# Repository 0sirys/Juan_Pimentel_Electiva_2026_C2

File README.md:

# Juan_Pimentel_Electiva_2026_C2

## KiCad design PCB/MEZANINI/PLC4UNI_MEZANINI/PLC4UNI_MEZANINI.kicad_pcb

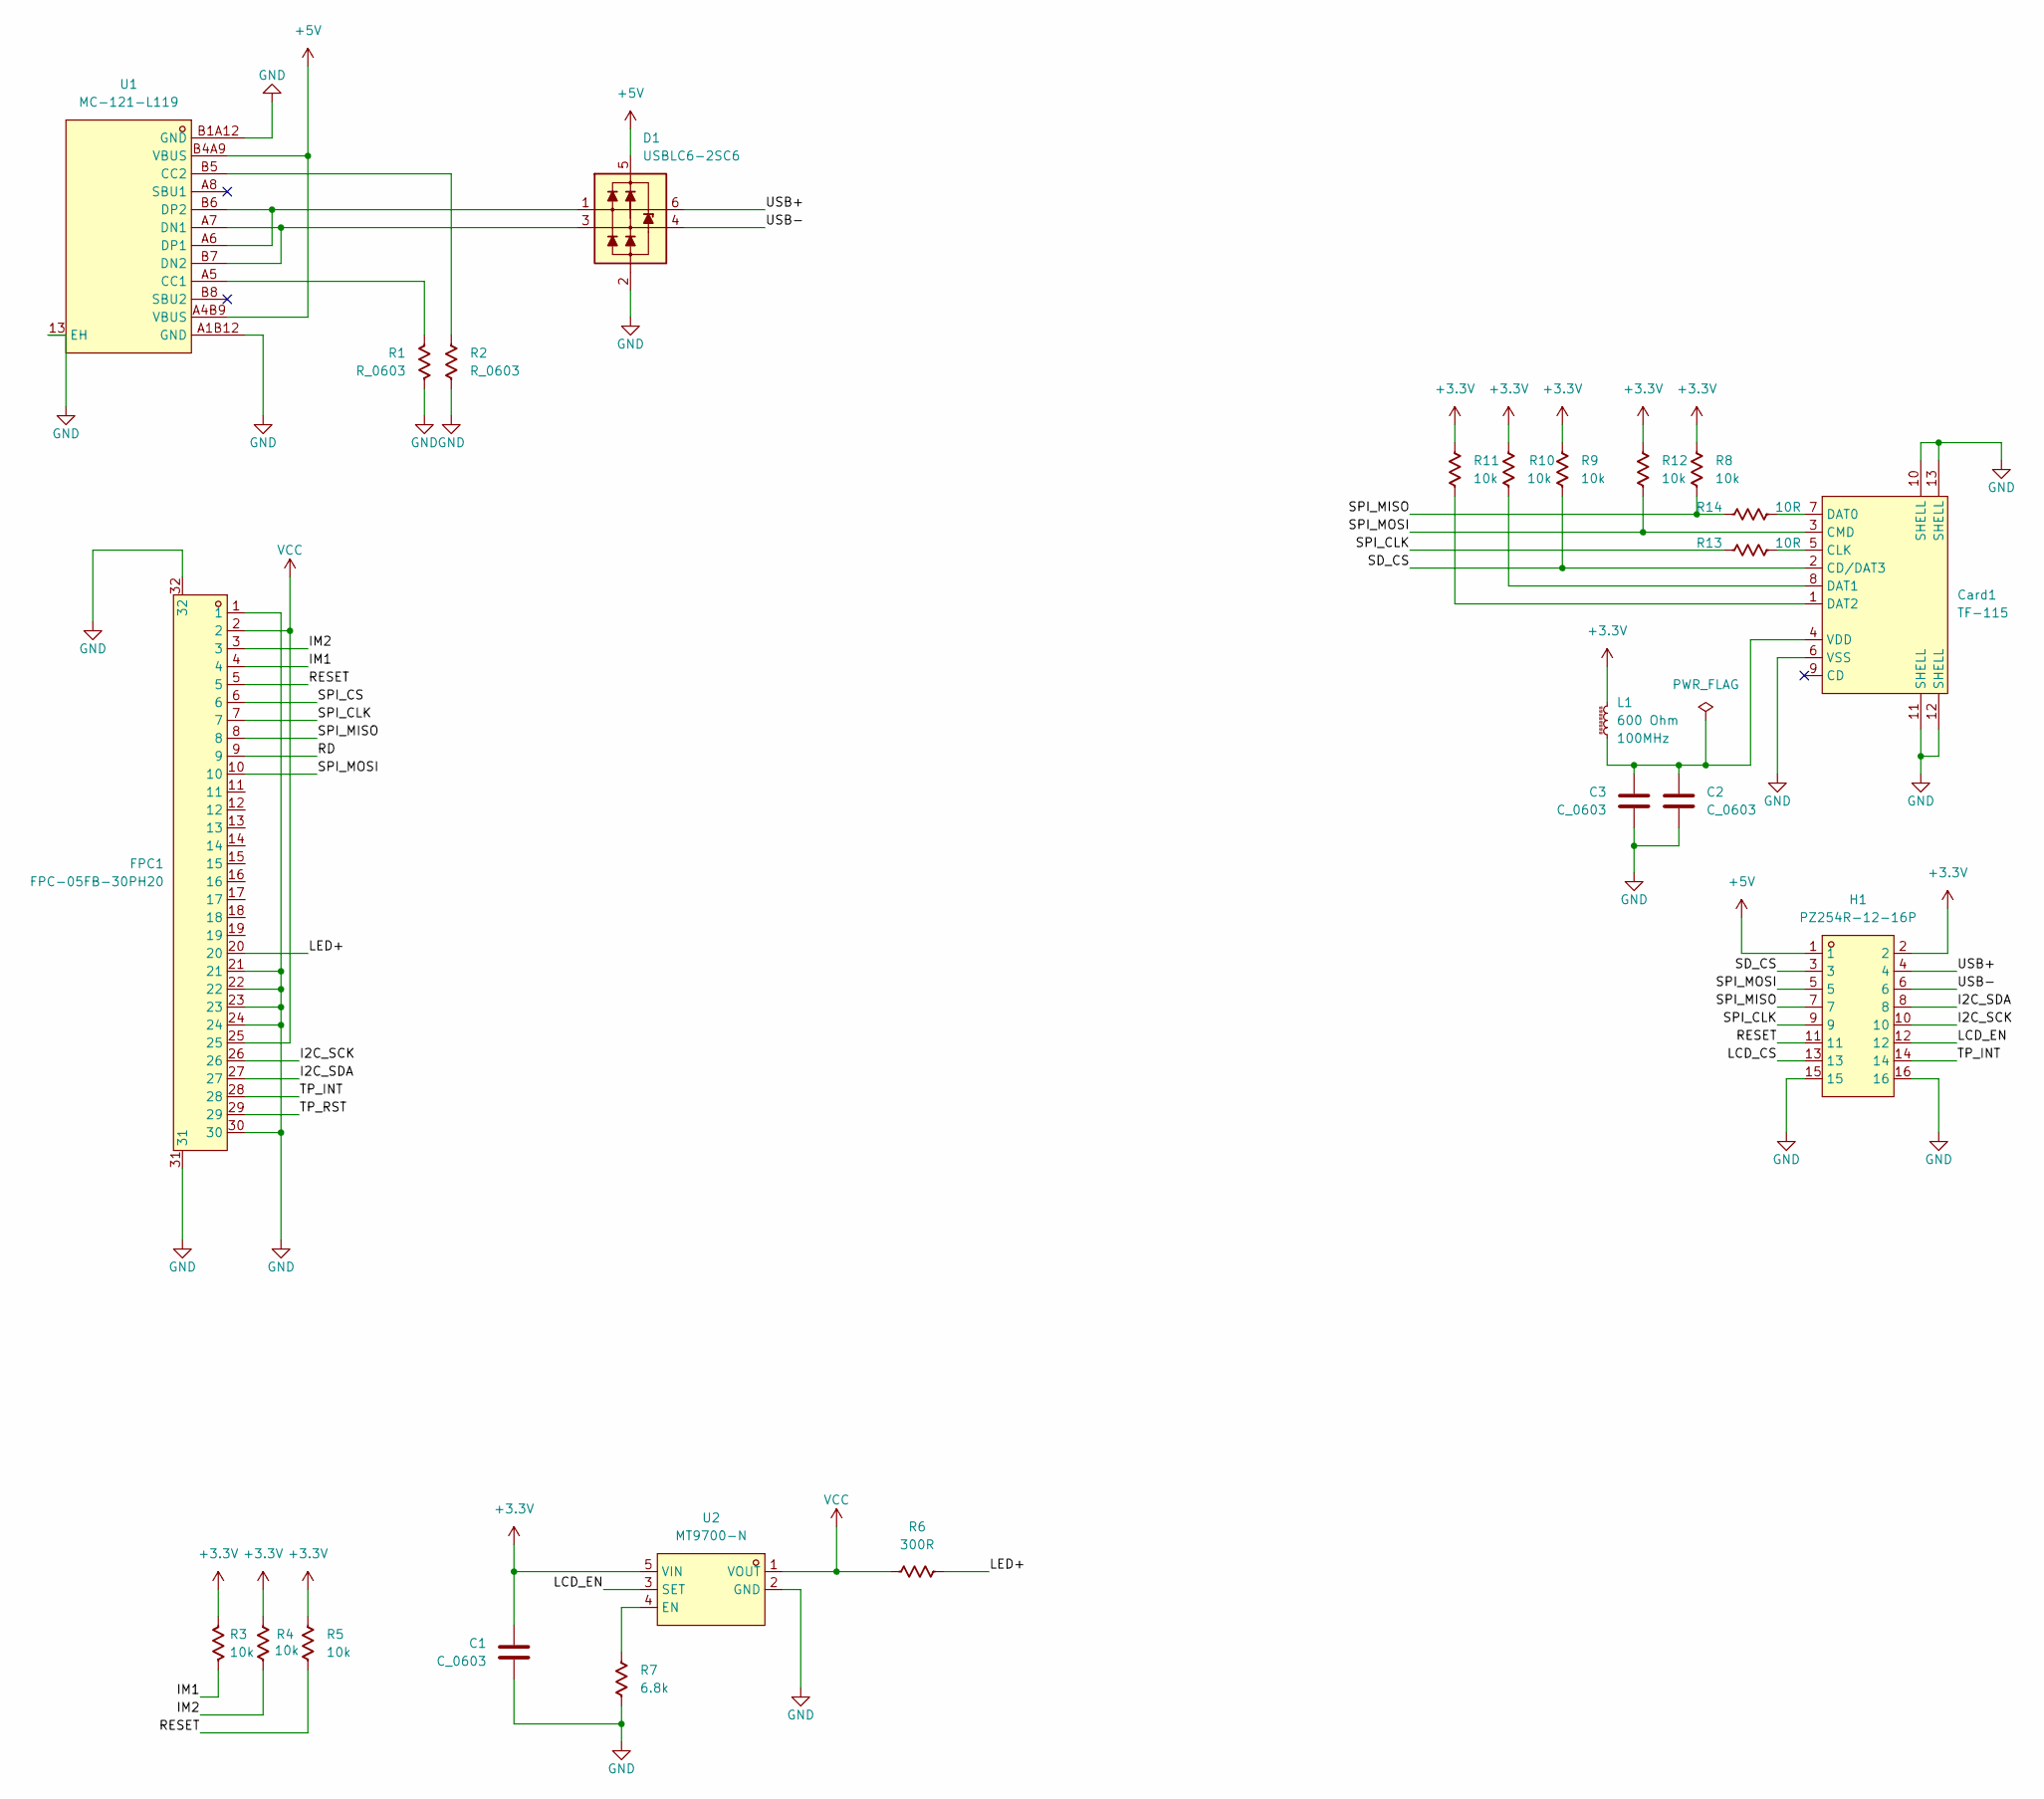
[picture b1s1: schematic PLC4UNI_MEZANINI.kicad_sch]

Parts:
C1, C2, C3: C_0603; C_0603_1608Metric
Card1: TF-115; TF-SMD_TF-115; MPN TF-115; LCSC Part C266620
D1: USBLC6-2SC6; SOT-23-6
FPC1: FPC-05FB-30PH20; FPC-SMD_30P-P0.50_FPC-05FB-30PH20; MPN FPC-05FB-30PH20; LCSC Part C2856833
H1: PZ254R-12-16P; HDR-TH_16P-P2.54-H-M-R2-C8-S2.54; MPN PZ254R-12-16P; LCSC Part C492436
L1: 600 Ohm; C_0805_2012Metric
R1, R2: R_0603; R_0603_1608Metric
R3, R4, R5, R8, R9, R10, R11, R12: 10k; R_0603_1608Metric
R6: 300R; R_0603_1608Metric
R7: 6.8k; R_0603_1608Metric
R13, R14: 10R; R_0603_1608Metric
U1: MC-121-L119; USB-C-SMD_HANBO_MC-121-L119; MPN MC-121-L119; LCSC Part C6332278
U2: MT9700-N; SOT-23-5_L2.9-W1.6-P0.95-LS2.9-BL; MPN MT9700-N; LCSC Part C42441843

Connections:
+3.3V: C1.1, H1.2, L1.2, R3.1, R4.1, R5.1, R8.1, R9.1, R10.1, R11.1, R12.1, U2.5 (VIN)
+5V: D1.5 (VP), H1.1, U1.A4B9 (VBUS), U1.B4A9 (VBUS)
/I2C_SCK: FPC1.26, H1.10
/I2C_SDA: FPC1.27, H1.8
/IM1: FPC1.4, R3.2
/IM2: FPC1.3, R4.2
/LCD_CS: H1.13
/LCD_EN: H1.12, U2.3 (SET)
/LED+: FPC1.20, R6.2
/RD: FPC1.9
/RESET: FPC1.5, H1.11, R5.2
/SD_CS: Card1.2 (CD/DAT3), H1.3, R9.2
/SPI_CLK: FPC1.7, H1.9, R13.1
/SPI_CS: FPC1.6
/SPI_MISO: FPC1.8, H1.7, R8.2, R14.1
/SPI_MOSI: Card1.3 (CMD), FPC1.10, H1.5, R12.2
/TP_INT: FPC1.28, H1.14
/TP_RST: FPC1.29
/USB+: D1.6 (L1), H1.4
/USB-: D1.4 (L2), H1.6
GND: C1.2, C2.2, C3.2, Card1.6 (VSS), Card1.10 (SHELL), Card1.11 (SHELL), Card1.12 (SHELL), Card1.13 (SHELL), D1.2 (VN), FPC1.1, FPC1.21, FPC1.22, FPC1.23, FPC1.24, FPC1.30, FPC1.31, FPC1.32, H1.15, H1.16, R1.2, R2.2, R7.1, U1.13 (EH), U1.A1B12 (GND), U1.B1A12 (GND), U2.2 (GND)
unnamed: Card1.5 (CLK), R13.2
unnamed: Card1.7 (DAT0), R14.2
unnamed: Card1.8 (DAT1), R10.2
unnamed: Card1.1 (DAT2), R11.2
unnamed: C2.1, C3.1, Card1.4 (VDD), L1.1
unnamed: R1.1, U1.A5 (CC1)
unnamed: R2.1, U1.B5 (CC2)
unnamed: D1.3 (L2), U1.A7 (DN1), U1.B7 (DN2)
unnamed: D1.1 (L1), U1.A6 (DP1), U1.B6 (DP2)
unnamed: R7.2, U2.4 (EN)
VCC: FPC1.2, FPC1.25, R6.1, U2.1 (VOUT)

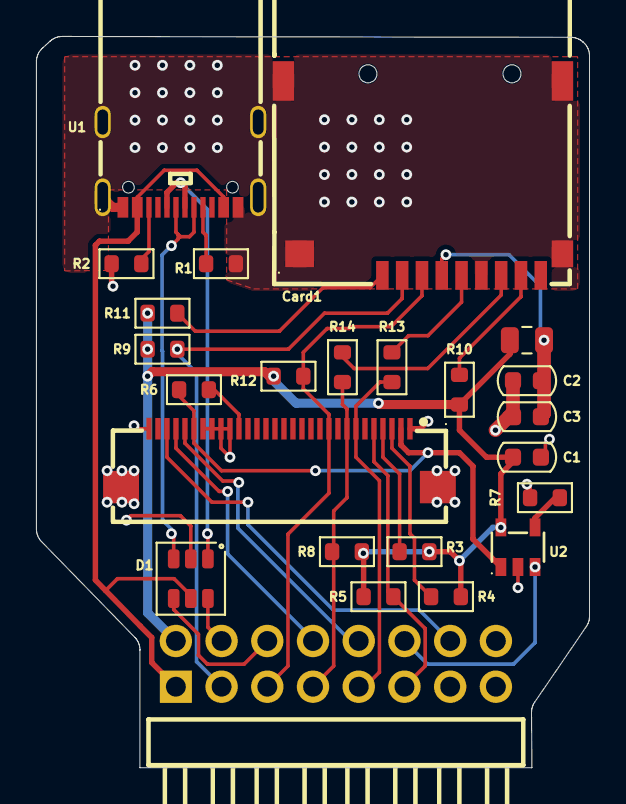
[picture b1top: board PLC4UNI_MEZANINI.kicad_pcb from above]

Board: 2 copper layers, 30.7 x 40.6 mm, 24 parts (0 on the bottom side), 28 nets.

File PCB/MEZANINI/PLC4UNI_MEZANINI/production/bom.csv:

Designator,Footprint,Quantity,Value,LCSC Part #
"C1, C2, C3",0603,3,C_0603,
CARD1,TF-SMD_TF-115,1,TF-115,C266620
D1,SOT-23-6,1,USBLC6-2SC6,
FPC1,FPC-SMD_30P-P0.50_FPC-05FB-30PH20,1,FPC-05FB-30PH20,C2856833
H1,HDR-TH_16P-P2.54-H-M-R2-C8-S2.54,1,PZ254R-12-16P,C492436
L1,0805,1,600 Ohm,
"R1, R2",0603,2,R_0603,
"R10, R11, R12, R3, R4, R5, R8, R9",0603,8,10k,
"R13, R14",0603,2,10R,
R6,0603,1,300R,
R7,0603,1,6.8k,
U1,USB-C-SMD_HANBO_MC-121-L119,1,MC-121-L119,C6332278
U2,SOT-23-5_L2.9-W1.6-P0.95-LS2.9-BL,1,MT9700-N,C42441843

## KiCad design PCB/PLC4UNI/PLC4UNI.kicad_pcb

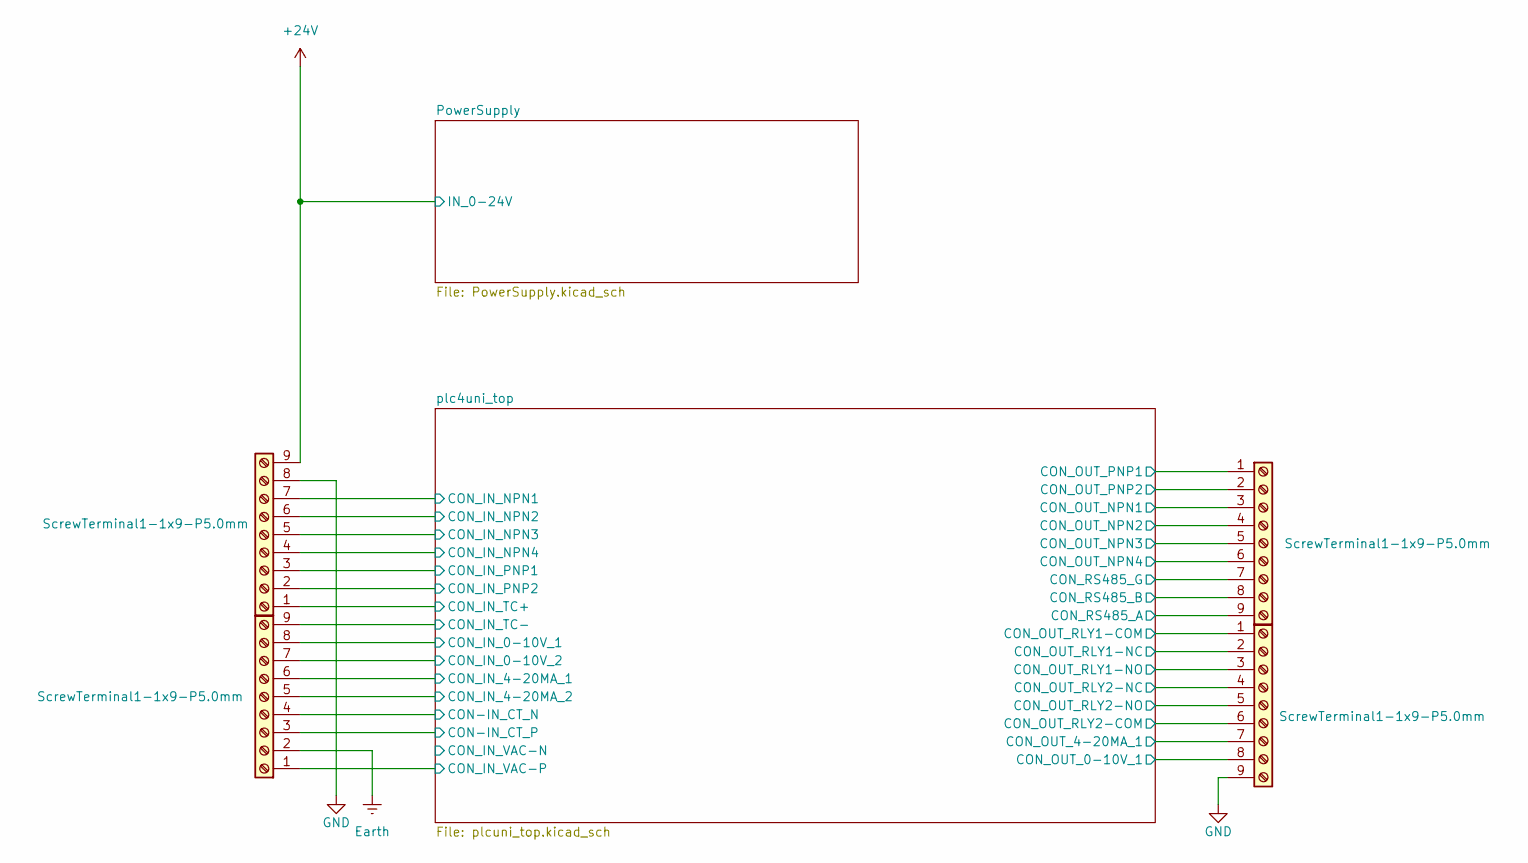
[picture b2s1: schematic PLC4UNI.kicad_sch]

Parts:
U1, U2, U3, U4: ScrewTerminal1-1x9-P5.0mm; CONN-TH_9P-P5.00_DB127V-5.0-9P-GN-S; MPN DB127V-5.0-9P-GN-S; LCSC Part C430627

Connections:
+24V: U1.9; also elsewhere on the board
/plc4uni_top/CON-IN_CT_N: U2.4; also elsewhere on the board
/plc4uni_top/CON-IN_CT_P: U2.3; also elsewhere on the board
/plc4uni_top/CON_IN_0-10V_1: U2.8; also elsewhere on the board
/plc4uni_top/CON_IN_0-10V_2: U2.7; also elsewhere on the board
/plc4uni_top/CON_IN_4-20MA_1: U2.6; also elsewhere on the board
/plc4uni_top/CON_IN_4-20MA_2: U2.5; also elsewhere on the board
/plc4uni_top/CON_IN_NPN1: U1.7; also elsewhere on the board
/plc4uni_top/CON_IN_NPN2: U1.6; also elsewhere on the board
/plc4uni_top/CON_IN_NPN3: U1.5; also elsewhere on the board
/plc4uni_top/CON_IN_NPN4: U1.4; also elsewhere on the board
/plc4uni_top/CON_IN_PNP1: U1.3; also elsewhere on the board
/plc4uni_top/CON_IN_PNP2: U1.2; also elsewhere on the board
/plc4uni_top/CON_IN_TC+: U1.1; also elsewhere on the board
/plc4uni_top/CON_IN_TC-: U2.9; also elsewhere on the board
/plc4uni_top/CON_IN_VAC-P: U2.1; also elsewhere on the board
/plc4uni_top/CON_OUT_0-10V_1: U4.8; also elsewhere on the board
/plc4uni_top/CON_OUT_4-20MA_1: U4.7; also elsewhere on the board
/plc4uni_top/CON_OUT_NPN1: U3.3; also elsewhere on the board
/plc4uni_top/CON_OUT_NPN2: U3.4; also elsewhere on the board
/plc4uni_top/CON_OUT_NPN3: U3.5; also elsewhere on the board
/plc4uni_top/CON_OUT_NPN4: U3.6; also elsewhere on the board
/plc4uni_top/CON_OUT_PNP1: U3.1; also elsewhere on the board
/plc4uni_top/CON_OUT_PNP2: U3.2; also elsewhere on the board
/plc4uni_top/CON_OUT_RLY1-COM: U4.1; also elsewhere on the board
/plc4uni_top/CON_OUT_RLY1-NC: U4.2; also elsewhere on the board
/plc4uni_top/CON_OUT_RLY1-NO: U4.3; also elsewhere on the board
/plc4uni_top/CON_OUT_RLY2-COM: U4.6; also elsewhere on the board
/plc4uni_top/CON_OUT_RLY2-NC: U4.4; also elsewhere on the board
/plc4uni_top/CON_OUT_RLY2-NO: U4.5; also elsewhere on the board
/plc4uni_top/CON_RS485_A: U3.9; also elsewhere on the board
/plc4uni_top/CON_RS485_B: U3.8; also elsewhere on the board
/plc4uni_top/CON_RS485_G: U3.7; also elsewhere on the board
Earth: U2.2; also elsewhere on the board
GND: U1.8, U4.9; also elsewhere on the board

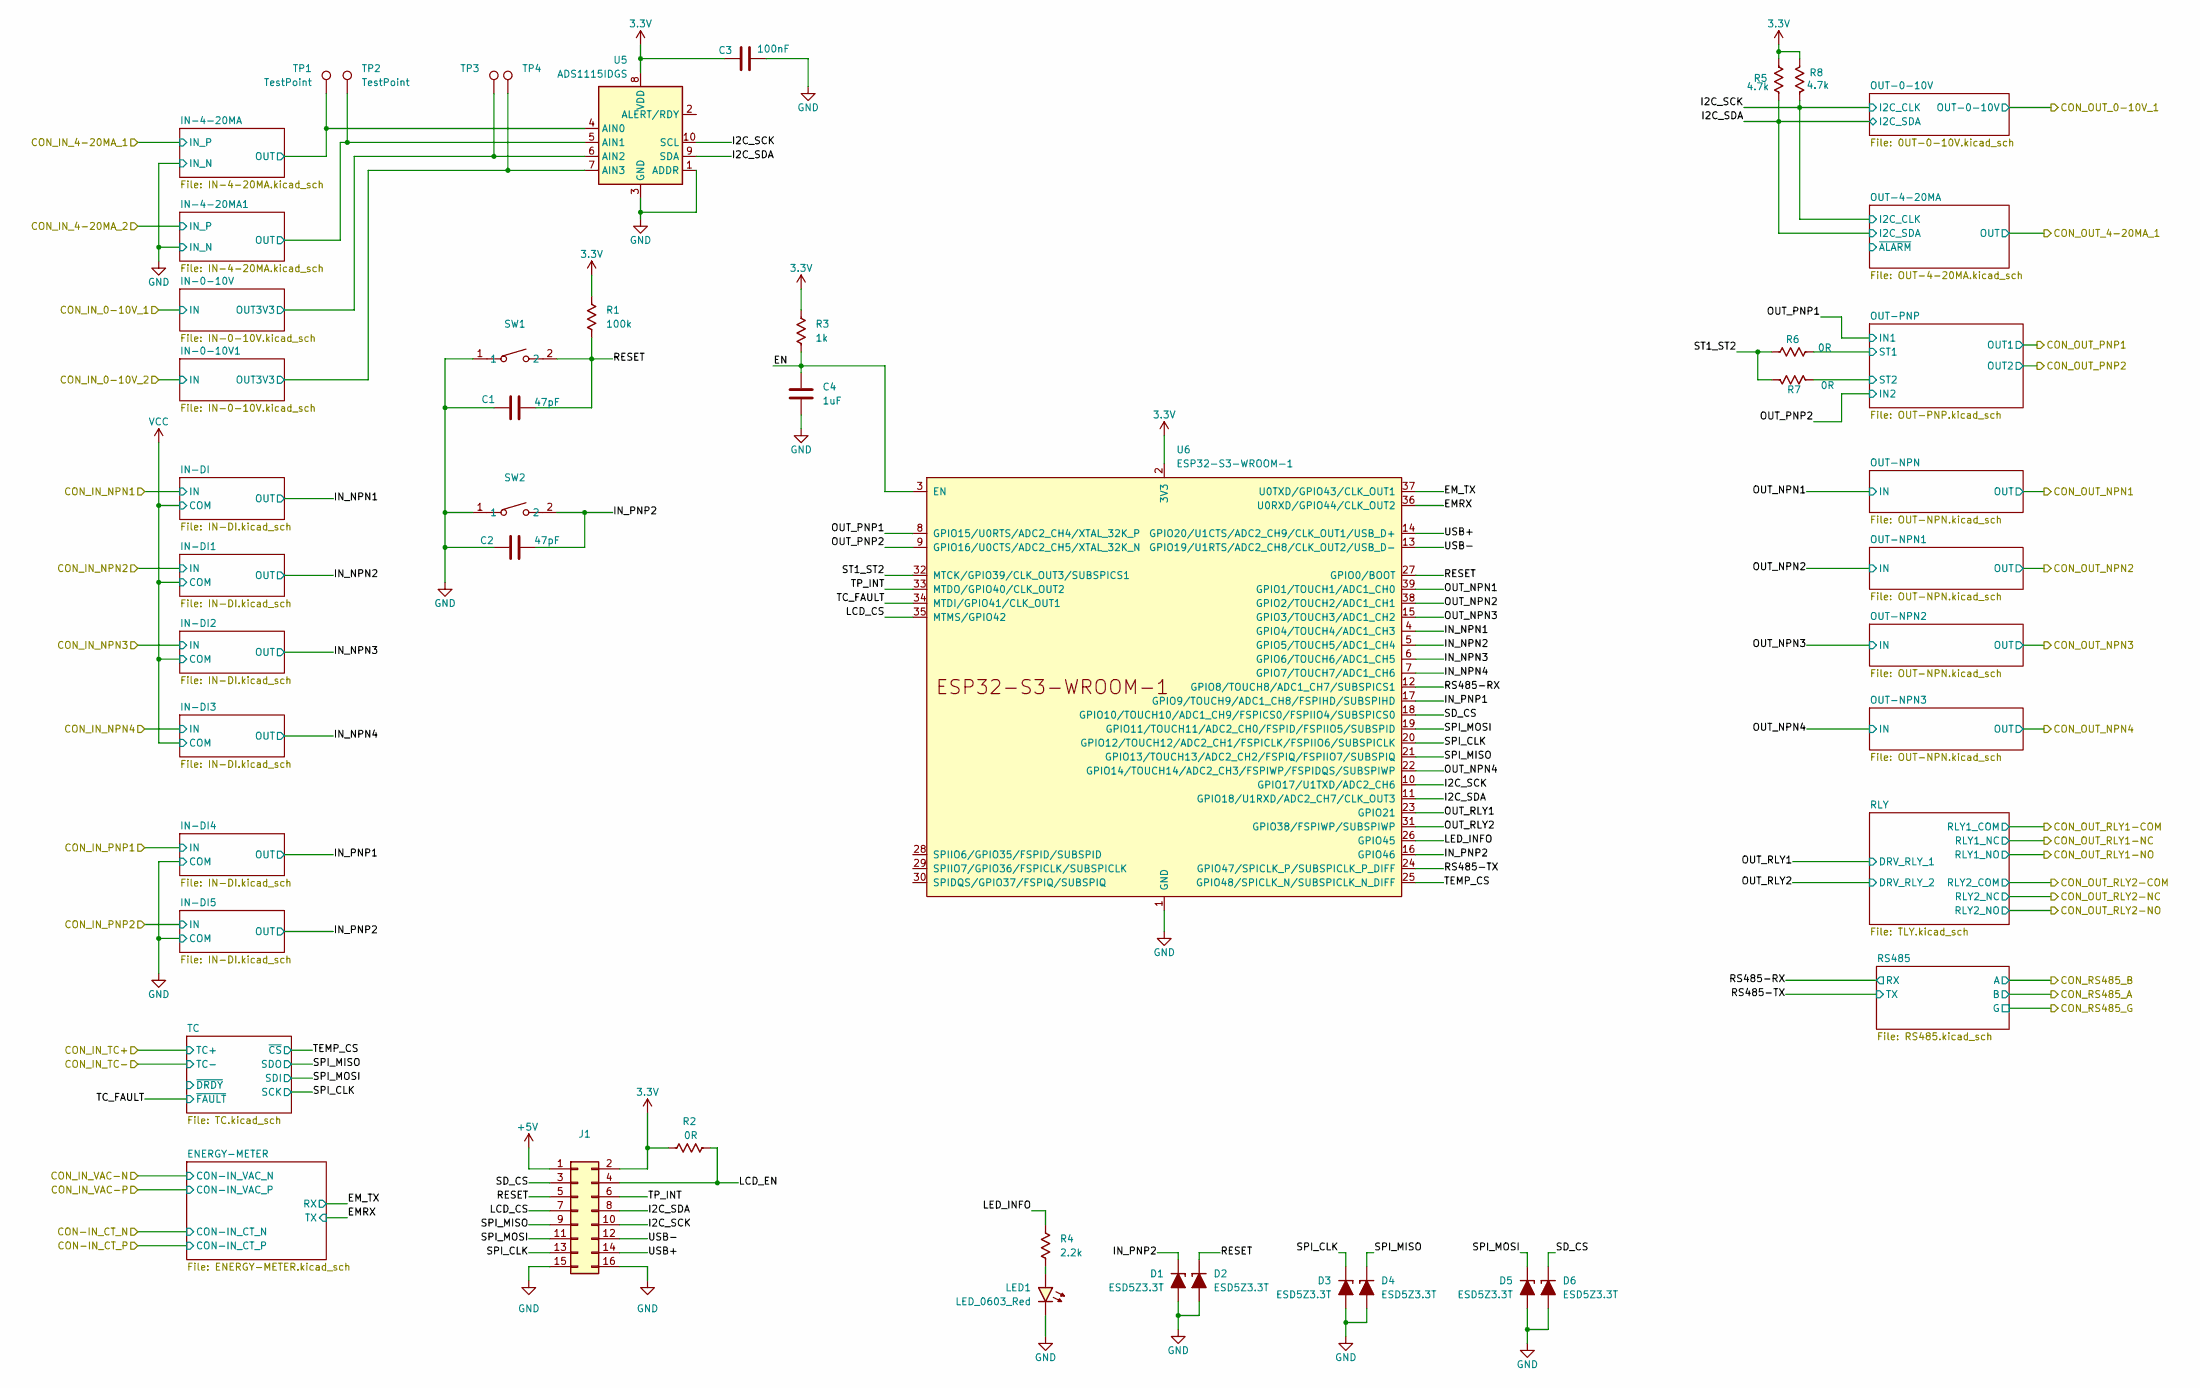
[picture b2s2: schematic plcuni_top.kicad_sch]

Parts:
C1, C2: 47pF; C_0603_1608Metric
C3: 100nF; C_0603_1608Metric
C4: 1uF; C_0603_1608Metric
D1, D2, D3, D4, D5, D6: ESD5Z3.3T; D_SOD-523
J1: Conn_02x08_Odd_Even; PinHeader_2x08_P2.54mm_Vertical
LED1: LED_0603_Red; LED_0603_1608Metric
R1: 100k; R_0603_1608Metric
R2, R6, R7: 0R; R_0603_1608Metric
R3: 1k; R_0603_1608Metric
R4: 2.2k; R_0603_1608Metric
R5, R8: 4.7k; R_0603_1608Metric
SW1, SW2: TS-1088-AR02016; SW-SMD_L3.9-W3.0-P4.45; MPN TS-1088-AR02016; LCSC Part C720477
TP1, TP2, TP3, TP4: TestPoint; TestPoint_THTPad_D1.5mm_Drill0.7mm
U5: ADS1115IDGS; TSSOP-10_3x3mm_P0.5mm
U6: ESP32-S3-WROOM-1

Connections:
3.3V: C3.1, J1.2, R1.1, R2.1, R3.1, R5.2, R8.2, U5.8 (VDD), U6.2 (3V3); also elsewhere on the board
/plc4uni_top/EMRX: U6.36 (U0RXD/GPIO44/CLK_OUT2); also elsewhere on the board
/plc4uni_top/EM_TX: U6.37 (U0TXD/GPIO43/CLK_OUT1); also elsewhere on the board
/plc4uni_top/EN: C4.1, R3.2, U6.3 (EN)
/plc4uni_top/I2C_SCK: J1.10, R8.1, U5.10 (SCL), U6.10 (GPIO17/U1TXD/ADC2_CH6); also elsewhere on the board
/plc4uni_top/I2C_SDA: J1.8, R5.1, U5.9 (SDA), U6.11 (GPIO18/U1RXD/ADC2_CH7/CLK_OUT3); also elsewhere on the board
/plc4uni_top/IN-0-10V1/OUT3V3: TP4.1 (1_1), U5.7 (AIN3); also elsewhere on the board
/plc4uni_top/IN-0-10V/OUT3V3: TP3.1 (1_1), U5.6 (AIN2); also elsewhere on the board
/plc4uni_top/IN-4-20MA1/OUT: TP2.1 (1_1), U5.5 (AIN1); also elsewhere on the board
/plc4uni_top/IN-4-20MA/OUT: TP1.1 (1_1), U5.4 (AIN0); also elsewhere on the board
/plc4uni_top/IN_NPN2: U6.39 (GPIO1/TOUCH1/ADC1_CH0); also elsewhere on the board
/plc4uni_top/IN_NPN3: U6.38 (GPIO2/TOUCH2/ADC1_CH1); also elsewhere on the board
/plc4uni_top/IN_NPN4: U6.15 (GPIO3/TOUCH3/ADC1_CH2); also elsewhere on the board
/plc4uni_top/LCD_CS: J1.7, U6.35 (MTMS/GPIO42)
/plc4uni_top/LCD_EN: J1.4, R2.2
/plc4uni_top/LED_INFO: R4.1, U6.26 (GPIO45)
/plc4uni_top/OUT-PNP/ST1: R6.2; also elsewhere on the board
/plc4uni_top/OUT-PNP/ST2: R7.2; also elsewhere on the board
/plc4uni_top/OUT_NPN1: U6.4 (GPIO4/TOUCH4/ADC1_CH3); also elsewhere on the board
/plc4uni_top/OUT_NPN2: U6.5 (GPIO5/TOUCH5/ADC1_CH4); also elsewhere on the board
/plc4uni_top/OUT_NPN3: U6.6 (GPIO6/TOUCH6/ADC1_CH5); also elsewhere on the board
/plc4uni_top/OUT_NPN4: U6.7 (GPIO7/TOUCH7/ADC1_CH6); also elsewhere on the board
/plc4uni_top/OUT_PNP1: U6.8 (GPIO15/U0RTS/ADC2_CH4/XTAL_32K_P); also elsewhere on the board
/plc4uni_top/OUT_PNP2: U6.9 (GPIO16/U0CTS/ADC2_CH5/XTAL_32K_N); also elsewhere on the board
/plc4uni_top/OUT_RLY1: U6.23 (GPIO21); also elsewhere on the board
/plc4uni_top/OUT_RLY2: U6.31 (GPIO38/FSPIWP/SUBSPIWP); also elsewhere on the board
/plc4uni_top/RS485-RX: U6.12 (GPIO8/TOUCH8/ADC1_CH7/SUBSPICS1); also elsewhere on the board
/plc4uni_top/RS485-TX: U6.17 (GPIO9/TOUCH9/ADC1_CH8/FSPIHD/SUBSPIHD); also elsewhere on the board
/plc4uni_top/SD_CS: D6.1 (K), J1.3, U6.18 (GPIO10/TOUCH10/ADC1_CH9/FSPICS0/FSPIIO4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)
/plc4uni_top/SPI_CLK: D3.1 (K), J1.13, U6.20 (GPIO12/TOUCH12/ADC2_CH1/FSPICLK/FSPIIO6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); also elsewhere on the board
/plc4uni_top/SPI_MISO: D4.1 (K), J1.9, U6.21 (GPIO13/TOUCH13/ADC2_CH2/FSPIQ/FSPIIO7/S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); also elsewhere on the board
/plc4uni_top/SPI_MOSI: D5.1 (K), J1.11, U6.19 (GPIO11/TOUCH11/ADC2_CH0/FSPID/FSPIIO5/S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); also elsewhere on the board
/plc4uni_top/ST1_ST2: R6.1, R7.1, U6.32 (MTCK/GPIO39/CLK_OUT3/SUBSPICS1)
/plc4uni_top/TC_FAULT: U6.34 (MTDI/GPIO41/CLK_OUT1); also elsewhere on the board
/plc4uni_top/TEMP_CS: U6.25 (GPIO48/SPICLK_N/SUBSPICLK_N_DIFF); also elsewhere on the board
/plc4uni_top/TP_INT: J1.6, U6.33 (MTDO/GPIO40/CLK_OUT2)
/plc4uni_top/USB+: J1.14, U6.14 (GPIO20/U1CTS/ADC2_CH9/CLK_OUT1/USB_D+)
/plc4uni_top/USB-: J1.12, U6.13 (GPIO19/U1RTS/ADC2_CH8/CLK_OUT2/USB_D-)
GND: C1.2, C2.2, C3.2, C4.2, D1.2 (A), D2.2 (A), D3.2 (A), D4.2 (A), D5.2 (A), D6.2 (A), J1.15, J1.16, LED1.1 (K), SW1.1, SW2.1, U5.1 (ADDR), U5.3 (GND), U6.1 (GND), U6.40 (GND), U6.41 (GND); also elsewhere on the board
unnamed: LED1.2 (A), R4.2

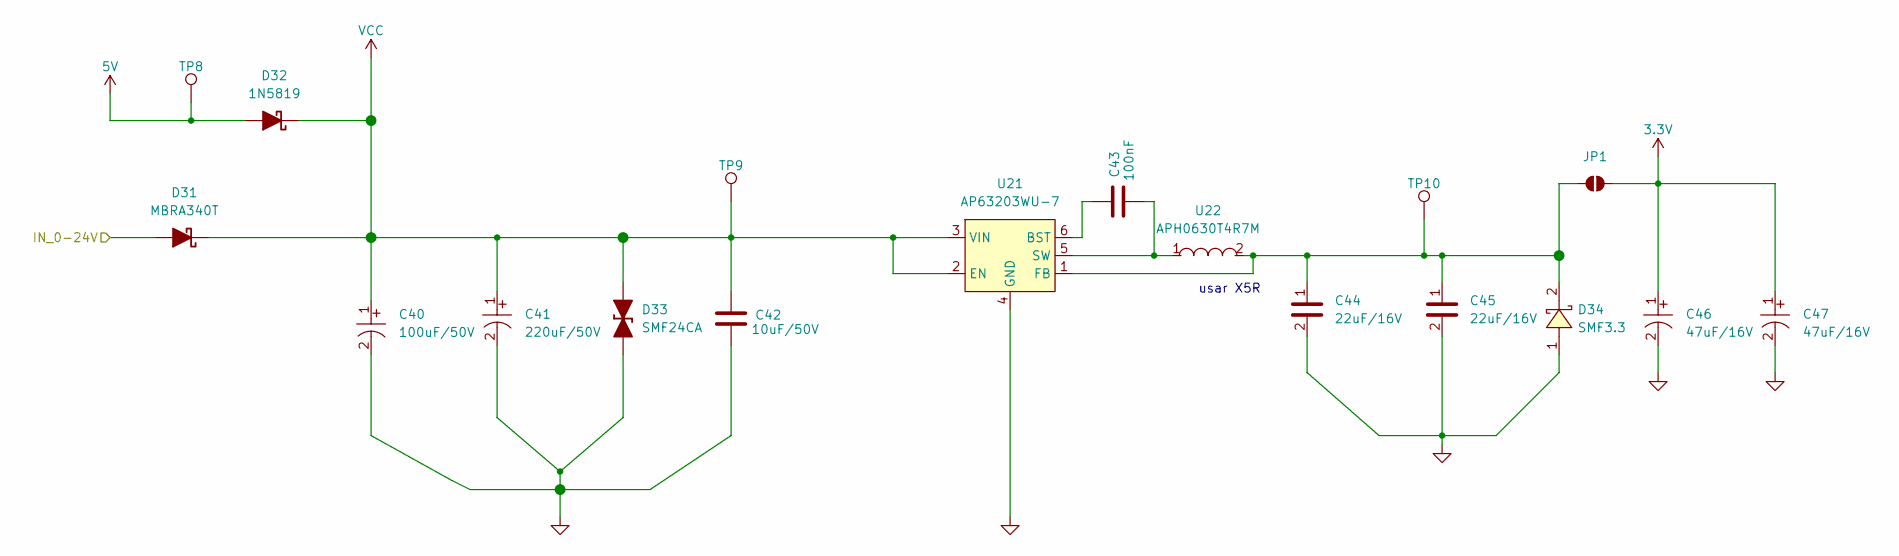
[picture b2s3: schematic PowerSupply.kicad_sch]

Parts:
C40: 100uF/50V; CAP-SMD_BD8.0-L8.3-W8.3-FD; MPN RVT1H101M0810; LCSC Part C72480
C41: 220uF/50V; CAP-SMD_BD10.0-L10.3-W10.3-LS11.3-FD; MPN UUD1H221MNL1GS; LCSC Part C125976
C42: 10uF/50V; C_0805_2012Metric; LCSC Part C440198
C43: 100nF; C_0805_2012Metric; LCSC Part C49678
C44, C45: 22uF/16V; C0805; MPN CL21A226MOQNNNE; LCSC Part C98190
C46, C47: 47uF/16V; CAP-SMD_BD6.3-L6.6-W6.6-FD; MPN UUD1C470MCL1GS; LCSC Part C340726
D31: MBRA340T; D_SMA
D32: 1N5819; D_DO-41_SOD81_P7.62mm_Horizontal
D33: SMF24CA; D_SOD-123F
D34: SMF3.3; SOD-123FL_L3.0-W1.9-LS3.7-FD; MPN SMF3.3; LCSC Part C2649858
JP1: Jumper_2_NO
TP8, TP9, TP10: 0.5mm; TestPoint-0.5mm
U21: AP63203WU-7; TSOT-26_L2.9-W1.6-P0.95-LS2.8-BL; MPN AP63203WU-7; LCSC Part C780769
U22: APH0630T4R7M; IND-SMD_L7.0-W6.6_APH0630; MPN APH0630T4R7M; LCSC Part C5349705

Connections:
3.3V: C46.1, C47.1, JP1.2 (B); also elsewhere on the board
+24V: D31.2 (A); also elsewhere on the board
GND: C40.2, C41.2, C42.2, C44.2, C45.2, C46.2, C47.2, D33.1 (K), D34.1, U21.4 (GND); also elsewhere on the board
unnamed: C44.1, C45.1, D34.2, JP1.1 (A), TP10.1 (1_1), U21.1 (FB), U22.2
unnamed: C43.1, U21.6 (BST)
unnamed: C43.2, U21.5 (SW), U22.1
VCC: C40.1, C41.1, C42.1, D31.1 (K), D32.1 (K), D33.2 (A), TP9.1 (1_1), U21.2 (EN), U21.3 (VIN); also elsewhere on the board

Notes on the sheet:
usar X5R

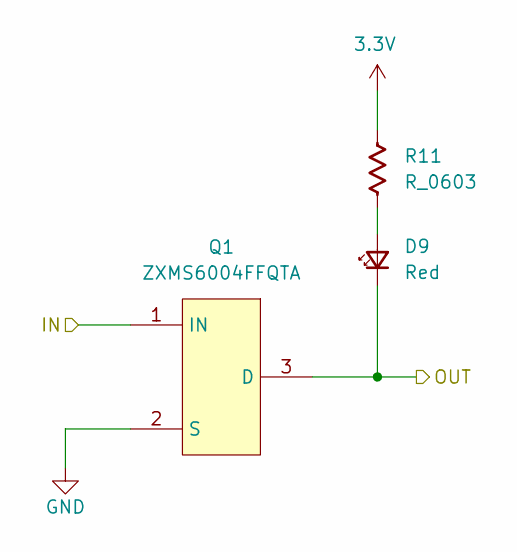
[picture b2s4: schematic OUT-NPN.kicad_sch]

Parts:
D9: Red; LED_0603_1608Metric_Red
Q1: ZXMS6004FFQTA; SOT-23F_L2.9-W1.8-P0.95-LS2.4-BR; MPN ZXMS6004FFQTA; LCSC Part C508259
R11: R_0603; R_0603_1608Metric

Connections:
3.3V: R11.1; also elsewhere on the board
/plc4uni_top/CON_OUT_NPN1: D9.1 (K), Q1.3 (D); also elsewhere on the board
/plc4uni_top/OUT_NPN1: Q1.1 (IN); also elsewhere on the board
GND: Q1.2 (S); also elsewhere on the board
unnamed: D9.2 (A), R11.2

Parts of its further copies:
D10, D11, D12: Red; LED_0603_1608Metric_Red
Q2, Q3, Q4: ZXMS6004FFQTA; SOT-23F_L2.9-W1.8-P0.95-LS2.4-BR; MPN ZXMS6004FFQTA; LCSC Part C508259
R12, R13, R14: R_0603; R_0603_1608Metric

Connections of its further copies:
3.3V: R12.1, R13.1, R14.1; also elsewhere on the board
/plc4uni_top/CON_OUT_NPN2: D10.1 (K), Q2.3 (D); also elsewhere on the board
/plc4uni_top/CON_OUT_NPN3: D11.1 (K), Q3.3 (D); also elsewhere on the board
/plc4uni_top/CON_OUT_NPN4: D12.1 (K), Q4.3 (D); also elsewhere on the board
/plc4uni_top/OUT_NPN2: Q2.1 (IN); also elsewhere on the board
/plc4uni_top/OUT_NPN3: Q3.1 (IN); also elsewhere on the board
/plc4uni_top/OUT_NPN4: Q4.1 (IN); also elsewhere on the board
GND: Q2.2 (S), Q3.2 (S), Q4.2 (S); also elsewhere on the board
unnamed: D10.2 (A), R12.2
unnamed: D11.2 (A), R13.2
unnamed: D12.2 (A), R14.2

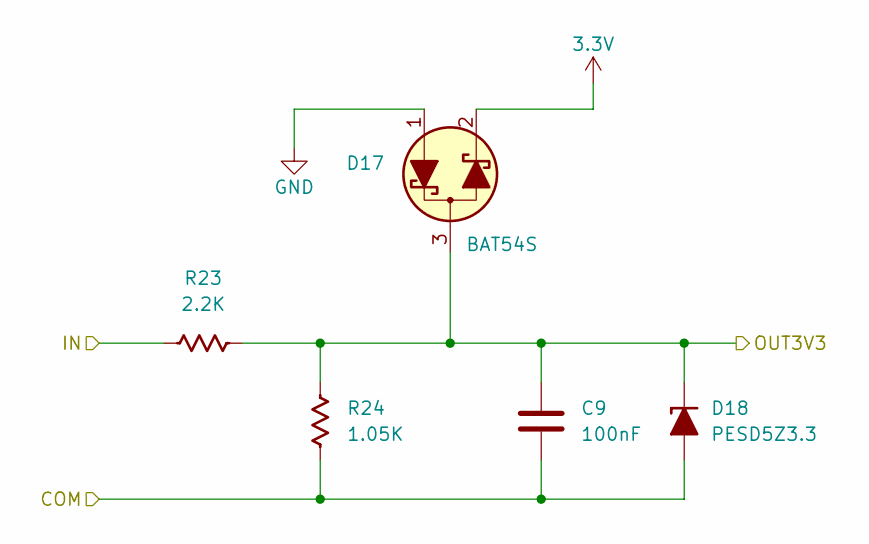
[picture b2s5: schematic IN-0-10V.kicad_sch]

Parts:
C9: 100nF; C_0603_1608Metric
D17: BAT54S; SOT-23
D18: PESD5Z3.3; D_SOD-523
R23: 2.2K; R_0603_1608Metric
R24: 1.05K; R_0603_1608Metric

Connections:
3.3V: D17.2 (K); also elsewhere on the board
/plc4uni_top/CON_IN_0-10V_1: R23.1; also elsewhere on the board
/plc4uni_top/IN-0-10V/COM: C9.2, D18.2 (A), R24.1
/plc4uni_top/IN-0-10V/OUT3V3: C9.1, D17.3 (C), D18.1 (K), R23.2, R24.2; also elsewhere on the board
GND: D17.1 (A); also elsewhere on the board

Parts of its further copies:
C10: 100nF; C_0603_1608Metric
D19: BAT54S; SOT-23
D20: PESD5Z3.3; D_SOD-523
R25: 2.2K; R_0603_1608Metric
R26: 1.05K; R_0603_1608Metric

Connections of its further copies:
3.3V: D19.2 (K); also elsewhere on the board
/plc4uni_top/CON_IN_0-10V_2: R25.1; also elsewhere on the board
/plc4uni_top/IN-0-10V1/COM: C10.2, D20.2 (A), R26.1
/plc4uni_top/IN-0-10V1/OUT3V3: C10.1, D19.3 (C), D20.1 (K), R25.2, R26.2; also elsewhere on the board
GND: D19.1 (A); also elsewhere on the board

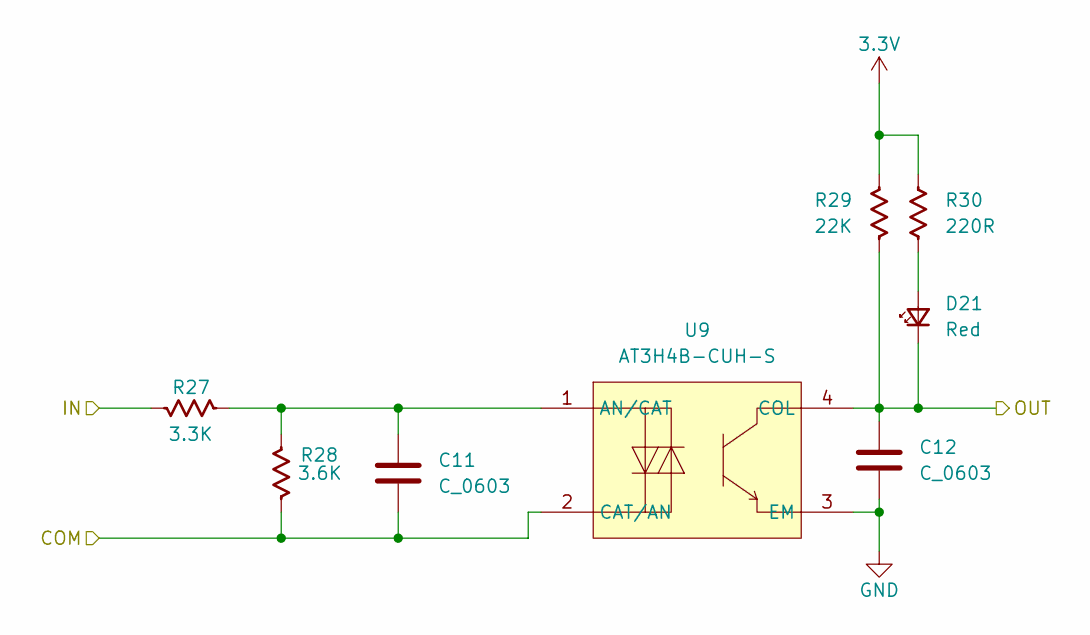
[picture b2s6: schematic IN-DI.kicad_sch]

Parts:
C11, C12: C_0603; C_0603_1608Metric
D21: Red; LED_0603_1608Metric_Red
R27: 3.3K; R_0603_1608Metric
R28: 3.6K; R_0603_1608Metric
R29: 22K; R_0603_1608Metric
R30: 220R; R_0603_1608Metric
U9: AT3H4B-CUH-S; SSOP-4_L2.7-W4.6-P1.27-LS7.0-TL; MPN AT3H4B-CuH-S; LCSC Part C20612635

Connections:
3.3V: R29.2, R30.2; also elsewhere on the board
/plc4uni_top/CON_IN_NPN1: R27.2; also elsewhere on the board
GND: C12.2, U9.3 (EM); also elsewhere on the board
unnamed: D21.2 (A), R30.1
unnamed: C11.1, R27.1, R28.1, U9.1 (AN/CAT)
VCC: C11.2, R28.2, U9.2 (CAT/AN); also elsewhere on the board

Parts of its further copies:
C13, C14, C15, C16, C17, C18, C19, C20, C21, C22: C_0603; C_0603_1608Metric
D22, D23, D24, D25, D26: Red; LED_0603_1608Metric_Red
R31, R35, R39, R43, R47: 3.3K; R_0603_1608Metric
R32, R36, R40, R44, R48: 3.6K; R_0603_1608Metric
R33, R37, R41, R45, R49: 22K; R_0603_1608Metric
R34, R38, R42, R46, R50: 220R; R_0603_1608Metric
U10, U11, U12, U13, U14: AT3H4B-CUH-S; SSOP-4_L2.7-W4.6-P1.27-LS7.0-TL; MPN AT3H4B-CuH-S; LCSC Part C20612635

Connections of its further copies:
3.3V: R33.2, R34.2, R37.2, R38.2, R41.2, R42.2, R45.2, R46.2, R49.2, R50.2; also elsewhere on the board
/plc4uni_top/CON_IN_NPN2: R31.2; also elsewhere on the board
/plc4uni_top/CON_IN_NPN3: R35.2; also elsewhere on the board
/plc4uni_top/CON_IN_NPN4: R39.2; also elsewhere on the board
/plc4uni_top/CON_IN_PNP1: R43.2; also elsewhere on the board
/plc4uni_top/CON_IN_PNP2: R47.2; also elsewhere on the board
/plc4uni_top/IN_NPN2: C14.1, D22.1 (K), R33.1, U10.4 (COL); also elsewhere on the board
/plc4uni_top/IN_NPN3: C16.1, D23.1 (K), R37.1, U11.4 (COL); also elsewhere on the board
/plc4uni_top/IN_NPN4: C18.1, D24.1 (K), R41.1, U12.4 (COL); also elsewhere on the board
GND: C14.2, C16.2, C18.2, C19.2, C20.2, C21.2, C22.2, R44.2, R48.2, U10.3 (EM), U11.3 (EM), U12.3 (EM), U13.2 (CAT/AN), U13.3 (EM), U14.2 (CAT/AN), U14.3 (EM); also elsewhere on the board
unnamed: D22.2 (A), R34.1
unnamed: D23.2 (A), R38.1
unnamed: D24.2 (A), R42.1
unnamed: D25.2 (A), R46.1
unnamed: D26.2 (A), R50.1
unnamed: C13.1, R31.1, R32.1, U10.1 (AN/CAT)
unnamed: C15.1, R35.1, R36.1, U11.1 (AN/CAT)
unnamed: C17.1, R39.1, R40.1, U12.1 (AN/CAT)
unnamed: C19.1, R43.1, R44.1, U13.1 (AN/CAT)
unnamed: C21.1, R47.1, R48.1, U14.1 (AN/CAT)
VCC: C13.2, C15.2, C17.2, R32.2, R36.2, R40.2, U10.2 (CAT/AN), U11.2 (CAT/AN), U12.2 (CAT/AN); also elsewhere on the board

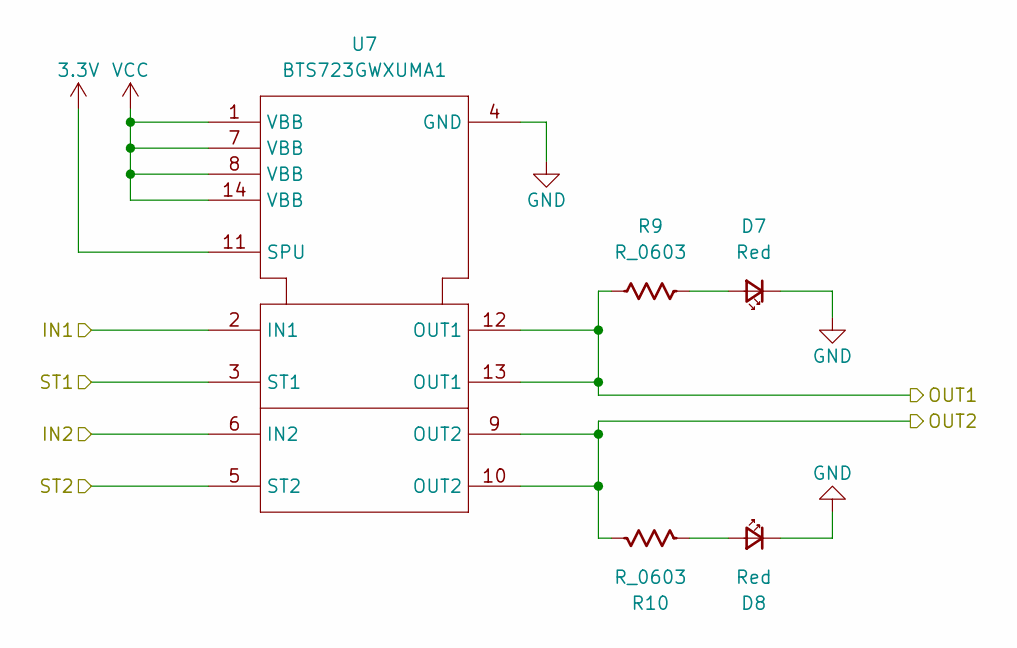
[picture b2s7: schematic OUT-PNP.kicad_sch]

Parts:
D7, D8: Red; LED_0603_1608Metric_Red
R9, R10: R_0603; R_0603_1608Metric
U7: BTS723GWXUMA1; SOIC-14_L8.7-W3.9-P1.27-LS6.0-BL; MPN BTS723GW; LCSC Part C67625

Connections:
3.3V: U7.11 (SPU); also elsewhere on the board
/plc4uni_top/CON_OUT_PNP1: R9.1, U7.12 (OUT1), U7.13 (OUT1); also elsewhere on the board
/plc4uni_top/CON_OUT_PNP2: R10.1, U7.9 (OUT2), U7.10 (OUT2); also elsewhere on the board
/plc4uni_top/OUT-PNP/ST1: U7.3 (ST1); also elsewhere on the board
/plc4uni_top/OUT-PNP/ST2: U7.5 (ST2); also elsewhere on the board
/plc4uni_top/OUT_PNP1: U7.2 (IN1); also elsewhere on the board
/plc4uni_top/OUT_PNP2: U7.6 (IN2); also elsewhere on the board
GND: D7.1 (K), D8.1 (K), U7.4 (GND); also elsewhere on the board
unnamed: D7.2 (A), R9.2
unnamed: D8.2 (A), R10.2
VCC: U7.1 (VBB), U7.7 (VBB), U7.8 (VBB), U7.14 (VBB); also elsewhere on the board

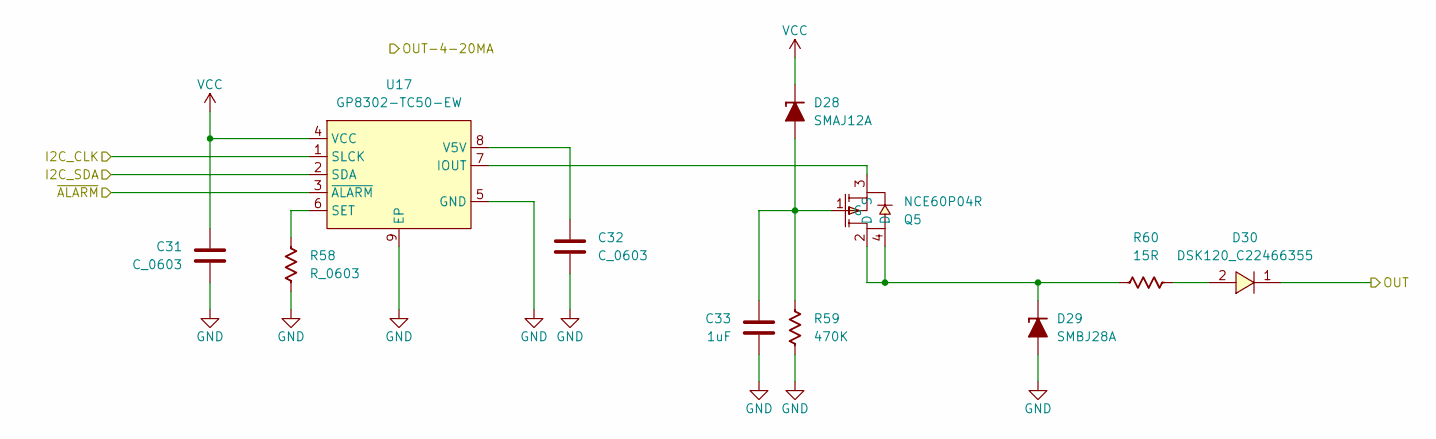
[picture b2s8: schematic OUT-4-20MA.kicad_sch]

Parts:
C31, C32: C_0603; C_0603_1608Metric
C33: 1uF; C_0603_1608Metric
D28: SMAJ12A; D_SMA
D29: SMBJ28A; D_SMB
D30: DSK120_C22466355; SOD-123FL_L2.7-W1.8-LS3.8-RD; MPN DSK120; LCSC Part C22466355
Q5: NCE60P04R; SOT-223-3_L6.5-W3.4-P2.30-LS7.0-BR; MPN NCE60P04R; LCSC Part C502855
R58: R_0603; R_0603_1608Metric
R59: 470K; R_0603_1608Metric
R60: 15R; R_0805_2012Metric
U17: GP8302-TC50-EW; ESOP-8_L4.9-W3.9-P1.27-LS6.0-BL-EP; MPN GP8302-TC50-EW; LCSC Part C2856295

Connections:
/plc4uni_top/CON_OUT_4-20MA_1: D30.1; also elsewhere on the board
/plc4uni_top/I2C_SCK: U17.1 (SLCK); also elsewhere on the board
/plc4uni_top/I2C_SDA: U17.2 (SDA); also elsewhere on the board
/plc4uni_top/OUT-4-20MA/~ALARM: U17.3 (~ALARM)
GND: C31.2, C32.2, C33.2, D29.2 (A), R58.2, R59.2, U17.5 (GND), U17.9 (EP); also elsewhere on the board
unnamed: C33.1, D28.2 (A), Q5.1 (G), R59.1
unnamed: D29.1 (K), Q5.2 (D), Q5.4 (D), R60.2
unnamed: D30.2, R60.1
unnamed: Q5.3 (S), U17.7 (IOUT)
unnamed: R58.1, U17.6 (SET)
unnamed: C32.1, U17.8 (V5V)
VCC: C31.1, D28.1 (K), U17.4 (VCC); also elsewhere on the board
